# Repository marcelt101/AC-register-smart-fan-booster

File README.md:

# AC register smart fan booster

Three quiet 80 mm 5 V fans (four 60 mm fans also fit) in each 4" × 10"
supply register. The original grille is replaced by a 3D-printed frame with a
coarse wire-mesh cover, for maximum airflow. The fans run only while the furnace/AC blower runs. Home Assistant
watches your HomeKit thermostat and switches them through a Pico W on a small
carrier PCB, one board per vent. A wall toggle switch gives manual ON / OFF /
AUTO. One USB-C phone charger powers each board.

```
vent-fans/
├── README.md                  ← you are here: design, BOM, install, tuning
├── wiring.md                  ← schematic in ASCII, connector pinouts, field wiring
├── esphome/vent-fans.yaml     ← smart firmware: Pico W + Home Assistant (validated, ESPHome 2026.11)
├── micropython/main.py        ← set-and-forget firmware: MicroPython, no Wi-Fi/HA, nothing to compile (same PCB)
├── homeassistant/automation.yaml
├── frame/                     ← 3D-printable fan frame: frame.scad, make_stl.sh, stl/, README
├── sim/                       ← ngspice models, ./run_all.sh, plot.py, results.txt, plots
└── kicad/                     ← KiCad 7 project: schematic, placed board, custom Pico W part
    └── tools/                 ← generators (gen_schematic.py, gen_pcb.py, check_netlist.py)
```

## What changed from the original spec, and why

| # | Original spec | v1 | Why (evidence in `sim/`) |
|---|---|---|---|
| 1 | 100 µF across the fans, no inductor | Add **one 100 µH inductor** between the fans and the MOSFET. That makes a proper low-side buck converter. | A capacitor across a low-side-switched load gets recharged to 5 V on every PWM pulse, so the fans saw nearly full voltage at any setting: **30 % duty still gave 89 % fan current**. With the inductor the fans get smooth DC ≈ duty × 5 V (30 % → 28 %, 60 % → 56 %, ripple ≈ 80 mV). See `plot_speed_vs_duty.png`. |
| 2 | Cap only across the fans | 100 µF + 10 µF **on the 5 V rail** (input) as well | Moving caps alone (no inductor) made it worse: every pulse recharged the fans' internal capacitors through the FET with **13–19 A spikes**. The buck version peaks at **0.4 A**. See `plot_waveforms_60pct.png`. |
| 3 | 25 kHz PWM | 40 kHz | Still inaudible. A 100 µH inductor is enough at this frequency (ripple ≈ 0.15 A). |
| 4 | Speed jumps instantly | **Soft-start in firmware**: 2 % every 20 ms | Going straight from 0 to 60 % rings the LC filter: **2.1 A** inductor peak. With the slew limiter it's **0.44 A**, so a small 1 A inductor never saturates. See `plot_powerup.png`. |
| 5 | IRLZ44N / AO3400 | **SI2302CDS** (Vishay, SOT-23; AO3400A also fits) | Fully on from the Pico's 3.3 V gate drive (75 mΩ max at 2.5 V). The simulations used an AO3400A model (~32 mΩ); the SI2302CDS's higher resistance still means under 50 mW even with 4 fans at full speed, so no heatsink. Chosen because Mouser stocks it. The IRLZ44N is only specified from 4 V gate drive and is huge. |
| 6 | Breadboard wiring | **Carrier PCB, 80 × 65 mm**, through-hole resistors and capacitors, **USB-C power socket**: Pico W socketed, 4 keyed fan headers, override-switch header, DS18B20 duct-probe header | Fewer loose joints in a dusty, warm, vibrating spot. Fans unplug for cleaning. |
| 7 | Automation used `delay` + `trigger.to_state` | `for:` on the triggers, re-sync on HA restart and when the board reconnects | The old version could leave fans running after an HA restart. `for:` doesn't drop a pending off when the thermostat chatters. |
| 8 | ESPHome reboots when HA is down | `reboot_timeout: 0s`, plus an on-board fallback from the duct probe | The fans keep working (or stay safely off) with HA down. |
| 9 | 3 fans | **Header for a 4th fan**; inductor spec raised to Isat ≥ 1.5 A, diode to SS24 | Four worst-case 0.25 A fans at full speed draw 0.84 A in simulation; the 5 V rail stays ≥ 4.87 V and the FET dissipates 23 mW. |
| 10 | No manual control | **ON-OFF-ON toggle** on J6, plus a **Mode** select (Auto / Force on / Force off) and **Manual speed** in HA | The switch wins over everything. Centre position = AUTO. Works with HA down, since it is read by the Pico. |

What stayed the same: Pico W, 5 V fans, one USB charger, HA in charge, 20 s
start delay, 30 s run-on, fans **off** if anything is unplugged or the Pico is
booting (10 k gate pull-down).

### Simulation summary (`sim/results.txt`, 3 × fans, 5.1 V charger + 1 m cable + the board's fuse)

| Circuit | duty → fan current (% of full) | FET peak (60 %) | 5 V rail min (30 %) |
|---|---|---|---|
| Original spec | 30→89, 60→97, 80→99 | 0.76 A | 4.30 V |
| Caps on rail, no L | 30→76, 60→90, 80→97 | **13.3 A** | 4.49 V |
| **v1 buck** | **30→28, 60→56, 80→78** | **0.39 A** | 5.04 V |
| v1 buck, **4 × 0.25 A fans** | 60 % → 2.74 V, 100 % → 4.63 V on the fans | 0.84 A (at 100 %) | 4.87 V (at 100 %); Pico VSYS 4.59 V |

The models are approximations: the AO3400A is a VDMOS fit to its datasheet, and
each fan is modelled as a reverse diode + 1 µF + 33 Ω + 1 mH. The comparison
between circuits is what matters, not the third digit. To re-run:
`cd sim && ./run_all.sh && python3 plot.py` (needs ngspice, numpy and matplotlib).

## Bill of materials

Shopping list with what to buy marked: [`BOM.md`](BOM.md) (and [`bom.csv`](bom.csv) for a spreadsheet).

| Ref | Qty | Part | Footprint | Notes |
|---|---|---|---|---|
| U1 | 1 | Raspberry Pi Pico W, plus 2× 20-pin female headers | 2×20 THT | Socketed, so it can be swapped or reflashed |
| J7 | 1 | USB-C receptacle, 16-pin (GCT USB4105-GF-A, Mouser 640-USB4105-GF-A) | `USB_C_Receptacle_GCT_USB4105` | Phone-charger input on the left edge. Shell lugs are through-hole; only VBUS, GND, CC1, CC2 are soldered to anything (data pins unconnected). Fine tip + flux. |
| R6, R7 | 2 | 5.1 kΩ ¼ W | THT axial, 7.62 mm | CC1/CC2 pull-downs. **Must be 5.1k**: without them a USB-C charger supplies no power. |
| F1 | 1 | Resettable fuse (PTC), 1.5–2 A hold, radial | 5.1 mm leads (Bourns MF-RHT200 footprint) | Protects the wiring in the wall if something shorts |
| D2 | 1 | 1N5819 Schottky | THT DO-41 | Feeds the Pico's VSYS from the 5 V rail; stops back-feed into your PC when you flash over the Pico's micro-USB |
| Q1 | 1 | SI2302CDS-T1-GE3 N-MOSFET (Vishay; AO3400A also fits) | SOT-23 | Logic-level, 20 V 2.9 A, 75 mΩ at 2.5 V gate. Stocked at Mouser |
| L1 | 1 | 100 µH shielded power inductor, **Isat ≥ 1.5 A, DCR ≤ 0.3 Ω** | Bourns SRR1260 (12.5 mm) | Sized for 4 fans. Check Isat on the datasheet of whatever you buy. |
| D1 | 1 | SS24 Schottky, 2 A 40 V (SS14 is fine for 3 fans) | SMA | Stripe (cathode) to +5 V |
| C1, C3 | 2 | 100 µF 10 V+ low-ESR electrolytic | radial 6.3 mm, 2.5 mm pitch | C1 = input, C3 = across the fans |
| C2 | 1 | 10 µF 16 V X7R ceramic, radial leads | THT, 5 mm lead spacing | Close to Q1/D1 |
| R1 | 1 | 100 Ω ¼ W | THT axial, 7.62 mm (0.3") | gate series resistor |
| R2 | 1 | 10 kΩ ¼ W | THT axial, 7.62 mm | gate pull-down |
| J1–J4 | 3–4 | 3-pin 2.54 mm fan header (KF2510 / Molex KK style) | `FanPinHeader_1x03` | J4 only for a 4th fan. 2-pin fan plugs fit pins 1–2. |
| J5, R3 | 1 + 1 | 3-pin header + 4.7 kΩ ¼ W | THT axial, 7.62 mm | For the DS18B20 probe (R3 is its pull-up) |
| J6, R4, R5 | 1 + 2 | 3-pin header + 1 kΩ ¼ W ×2 | THT axial, 7.62 mm | Override switch. R4/R5 protect the Pico from the off-board wire. |
| SW1 | 1 | ON-OFF-ON (centre-off) SPDT toggle, e.g. MTS-103, + 3-core cable + 3-pin 2.54 mm housing | off-board | Drawn on the schematic in the dashed off-board box. Mount on the wall plate, grille or a small box. Any low-voltage switch works (3.3 V, < 1 mA). |
| — | 4 | 80 mm **5 V** fans, 25 mm thick, sleeve/hydraulic bearing, ≤ 0.25 A | | 4 fit in this vent. Pick the lowest-RPM/dBA listing. |
| RV1, C4 | 1 + 1 | 20 kΩ trimpot (10k–50k all work; Bourns 3296W footprint) + 100 nF | THT | Standalone firmware: fan speed |
| SW2 | 1 | 6 mm tactile button | THT | Standalone firmware: LEARN |
| D3, R8 | 1 + 1 | 3 mm LED + 330 Ω | THT | Standalone firmware: status |
| — | 1 | USB-C phone charger (5 V, **≥ 2 A**) + USB-C cable | | Plugs into J7 on the board. Any USB-C charger works; the board asks for plain 5 V. |
| — | 1 | Waterproof DS18B20 probe (stainless tube, 1–3 m cable) + 3-pin 2.54 mm housing | | Duct temperature: shown in HA, runs the fans when HA is down |
| — | 1 | Wire mesh, **¼" (6 mm) openings or smaller**: hardware cloth, or expanded metal for a floor vent | | Replaces the grille; cut to the size `frame/make_stl.sh` prints. See [`frame/README.md`](frame/README.md). |
| — | 8–10 | M3 × 8 countersunk screws (+ 4 × M3 × 10 and nuts for the split frame) | | Hold the printed bezel and mesh down |

Total draw per board: ≈ 0.5 A at full speed with 3 typical fans, up to ~1 A with
4 worst-case fans.

**Fans per vent:** 3 × 80 mm uses 240 mm of the 254 mm (10") opening.
**4 × 80 mm (320 mm) cannot fit**; four fans means 60 mm fans (4 × 60 = 240 mm).
Three 80 mm fans move noticeably more air than four 60 mm ones, so 3 × 80 is the
default. The board takes either.

## Build

1. **PCB**: open `kicad/vent_fans.kicad_pro` in KiCad 7 or later. The
   schematic is complete and the board is placed with nets assigned. You do the
   routing; see [Routing the board](#routing-the-board).
2. **Solder** the three surface-mount parts first: Q1 (SOT-23), D1 (SMA) and
   L1. They are all large enough for a normal iron. Then fit the through-hole
   resistors, capacitors, headers and Pico sockets. Bend the resistor leads to
   7.62 mm (0.3").
   Check the polarity of C1/C3 (+) and D1 (stripe toward the +5V side).
3. **Firmware**: in the ESPHome add-on on your Proxmox HA, create a new device
   per vent, paste `esphome/vent-fans.yaml`, change `name` / `friendly_name` at
   the top (e.g. `vent-fans-living`), add the secrets (`esphome/secrets.example.yaml`
   shows the names), plug the Pico W's own micro-USB into your PC and install.
   This is safe with the charger also plugged into J7, thanks to D2. After that,
   updates go over Wi-Fi.
4. **Bench test** before it goes in the wall. Plug the charger into the
   board's USB-C socket (J7) with the fans attached. In HA, turn on `fan.vent_fans`: the fans should ramp up over about
   a second. Measure across a fan connector (pin 2 to pin 1): ≈ 2.7 V at 1 %,
   ≈ 4 V at 60 %, ≈ 4.9 V at 100 %.
5. **Automation**: in HA, go to Developer Tools → States, filter `climate.`, and
   find your thermostat. Check that it has an `hvac_action` attribute that
   changes between `idle` and `heating`/`cooling`. HomeKit Controller thermostats
   normally do. Paste `homeassistant/automation.yaml` into a new automation and
   replace `climate.thermostat` (3 places). List each vent's fan entity in both
   fan lists.
6. **Override switch**: wire the toggle to J6 with 3 conductors: centre lug →
   pin 2 (GND), one outer lug → pin 1 (ON), the other → pin 3 (OFF). Flip it and
   watch the board's **Control source** sensor in HA change. You can also
   override from your phone with the **Mode** select, and set the override speed
   with **Manual speed** (default 100 %).
7. **Frame and mesh cover** (replaces the grille): see
   [`frame/README.md`](frame/README.md). Measure the opening, then
   `frame/make_stl.sh <width> <height> <fan> <count> <floor|wall>` writes
   print-ready STLs (base + bezel, one-piece and split), the mesh cut size and
   the screw count. PETG or ASA, no supports.

## Routing the board

The board in `kicad/vent_fans.kicad_pcb` is 80 × 65 mm and two-layer. It already
has a GND pour on both layers and a copper keep-out under the Pico W antenna.
The `Power` net class (0.8 mm tracks) covers VBUS_IN, +5V, GND, FAN- and SW. Signals
default to 0.3 mm.

1. Open the PCB and press **B** to refill zones. The ratsnest shows the 39
   connections still to route.
2. Route the **switching loop** first and keep it tiny: C2 → D1 cathode, D1
   anode → Q1 drain, Q1 source → GND via next to C2's GND pad. This is the only
   fast-edge loop on the board.
3. SW (Q1 drain / D1 anode / L1 pin 2) is the noisy node. Keep it short and
   on the top layer, with no long runs.
4. Power in: J7's four VBUS pads (A4, A9, B4, B9) → F1 → +5V. Tie the four
   GND pads (A1, A12, B1, B12) and the four shell lugs to the GND pour. Leave
   D+, D− and SBU unconnected. R6 from CC1 (A5) to GND and R7
   from CC2 (B5) to GND, kept close to the socket.
5. +5V: from F1 to C1 and C2, then on to the fan headers' pin 2 and C3+. Use
   0.8 mm or wider. Also +5V → D2 anode, and D2 cathode → Pico pin 39 (VSYS,
   top-left, second pad from the USB end). Leave Pico pin 40 (VBUS) unconnected.
6. FAN-: from L1 pin 1 to C3−, then to pin 1 of J1–J4.
7. GP15 (bottom-right Pico pad) → R1 → gate. R2 goes from gate to GND.
8. Duct probe: GP16 → J5 pin 2 → R3 → 3V3 (Pico pin 36).
9. Override: GP18 (Pico pin 24) → R4 → J6 pin 1 and GP17 (pin 22) → R5 → J6
   pin 3. Both pads are on the top row next to the antenna end. Route them on
   the bottom layer under the Pico, staying outside the keep-out, or along the
   top edge.
10. Stitch the two GND pours with a few vias, keeping them away from the
   antenna keep-out. Run **Inspect → Design Rules Checker** until it's clean.
11. **File → Fabrication Outputs → Gerbers + Drill**, zip them and order (any
   2-layer, 1.6 mm, HASL service).

`kicad/tools/` regenerates everything from one parts table, if you want to change
a part:
`python3 tools/gen_schematic.py && python3 tools/check_netlist.py && /usr/bin/python3 tools/gen_pcb.py`.
Note that this overwrites any routing you've done, so only use it before you route.

## Tuning

- **Speed**: `speed: 60` in the automation. With smooth DC the fans are much
  quieter at a given speed than with chopped PWM. Try 30–60 %.
- **Fans won't start at low speed**: raise `min_power` (0.55 ≈ 2.7 V) in
  `vent-fans.yaml`.
- **Delays**: the `for:` values in the automation (20 s on, 30 s run-on).
- **Your thermostat only shows `idle`/`heating`** (no `cooling`, or the
  attribute is missing): make the HA automation trigger on the board's
  **Duct temperature** sensor instead (same thresholds as the fallback).
- **Duct-probe fallback thresholds**: `duct_hot`, `duct_cold`, `duct_idle_low`
  and `duct_idle_high` at the top of `vent-fans.yaml`. Watch **Duct
  temperature** in HA for a day of heating or cooling, then set them between
  what you see with the blower running and with it off.

## Standalone (set-and-forget) version

The same PCB runs without Wi-Fi or Home Assistant on
[MicroPython](micropython/README.md): put MicroPython on the Pico, then copy
[`micropython/main.py`](micropython/main.py) onto it with Thonny. Nothing to
compile. A plain Pico (no W) is enough; Pico, Pico W, Pico 2 and Pico 2 W all
fit the same socket and use the same pins (only internal pins GP23/24/25/29
differ, and the firmware leaves them alone). Install steps, LED codes and how
to edit the settings are in [`micropython/README.md`](micropython/README.md).

**How it decides:** the duct probe watches the supply air. Fans start when the
air is hotter than the **heating threshold** or colder than the **cooling
threshold** for 20 s, and stop once it has been back between them (minus a
2 °C margin) for 60 s. The fans can't fool it: they move air, but they can't
make it hot or cold. It needs a duct that rests near room temperature (a
basement, crawlspace or slab, not an attic). It doesn't react to fan-only mode
(blower with no heating or cooling).

**Set-up, once:**
1. **Speed:** flip the override switch to ON. Turn the SPEED trimpot (RV1)
   until the fans are as quiet as you like while still pushing air. Flip back
   to the centre (AUTO).
2. **Heating threshold:** in winter, while the furnace is heating, press
   **LEARN** once. The LED blinks 3×.
3. **Cooling threshold:** in summer, while the AC is cooling, press **LEARN**
   once. The LED blinks 2×.

Each press sets that threshold halfway between the duct's resting temperature
(tracked while nothing is running) and the current temperature, and saves it.
Until you calibrate, the defaults are 32 °C (90 °F) and 16 °C (61 °F).
- **10 blinks:** the air isn't hot or cold enough yet to learn from, or the
  board only just started; try again in a few minutes.
- **Hold LEARN 5 s:** back to the defaults (5 blinks).
- **Status LED:** on = fans running, off = idle, slow blink = no probe (fans
  stay off in AUTO).
- **USB log:** connect Thonny to see the duct, resting and threshold
  temperatures every 30 s (see `micropython/README.md`).

## Safety and install notes

- **FAN- is not ground.** The fans' black wires sit at about 5 V minus the fan
  voltage. Never tie a fan's black wire to GND, the metal duct or the Pico.
- Keep the PCB and charger outside the duct, in the wall cavity or a small box
  next to the boot. Only the fan leads (and the probe) go into the airstream. Use
  plenum-rated cable if your local code requires it for runs inside the duct.
- Keep fans away from electric heat strips. With a heat pump or electric
  furnace, mount the fans at the register end only.
- Mount fans on foam or rubber grommets, seal the frame with foam
  weatherstrip, and have the fans blow into the room.
- **The mesh is the finger guard.** Keep its openings at ¼" (6 mm) or smaller,
  and always screw the bezel down before running the fans.
- If HA is down, the board runs the fans from the duct probe. If the probe is
  unplugged as well, the fans stay off. A Pico crash or unplugged charger also
  means fans off.
- **Duct probe**: drill a 6–7 mm hole in the side of the boot or duct, a few
  inches upstream of the fans. Push the probe tip into the airstream and seal
  the hole with foil HVAC tape. Keep it out of direct contact with the metal.

## Why Wi-Fi and not Zigbee

Your Zigbee network through HA would work, but it doesn't make this simpler.
There is no Pico + Zigbee option, and an ESP32-C6/H2 running Zigbee firmware is
harder to set up than ESPHome over Wi-Fi. It would also give up the
Mode / Manual speed / Control source entities and the on-board fallback.

The one real Zigbee simplification is a different product altogether: a Zigbee
smart plug feeding a USB charger, with the fans wired straight to USB. That
means no PCB, but also no speed control, no soft start and no override switch,
and the fans always run at full 5 V. The PCB design is better for quiet fans.

## Still open

- **Boot depth**: the frame needs about 30 mm below the floor for 25 mm fans.
- **Thermostat model**: to confirm it exposes `hvac_action` through HomeKit.

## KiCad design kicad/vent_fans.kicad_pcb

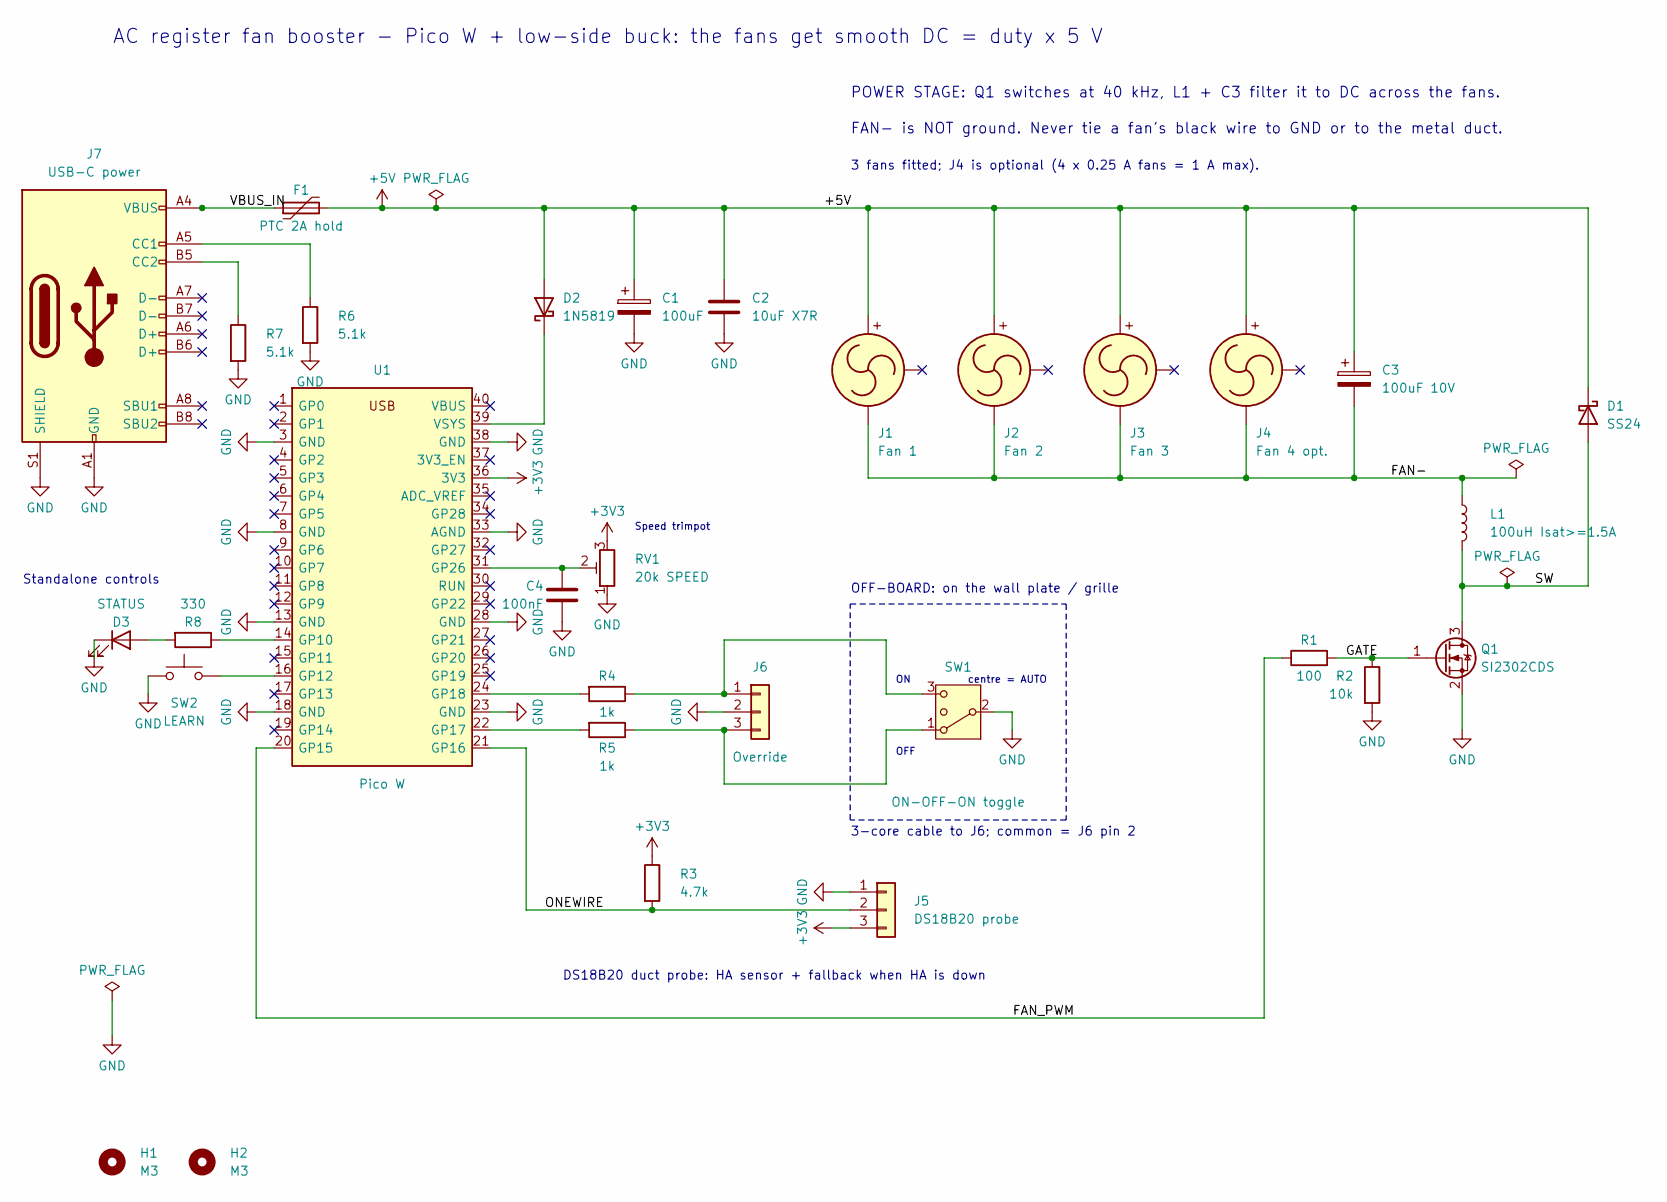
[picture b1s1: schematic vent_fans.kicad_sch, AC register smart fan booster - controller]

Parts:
C1: 100uF; CP_Radial_D6.3mm_P2.50mm
C2: 10uF X7R; C_Disc_D5.0mm_W2.5mm_P5.00mm
C3: 100uF 10V; CP_Radial_D6.3mm_P2.50mm
C4: 100nF; C_Disc_D3.0mm_W1.6mm_P2.50mm
D1: SS24; D_SMA
D2: 1N5819; D_DO-41_SOD81_P10.16mm_Horizontal
D3: STATUS; LED_D3.0mm
F1: PTC 2A hold; Fuse_Bourns_MF-RHT200
H1, H2: M3; MountingHole_3.2mm_M3
J1: Fan 1; FanPinHeader_1x03_P2.54mm_Vertical
J2: Fan 2; FanPinHeader_1x03_P2.54mm_Vertical
J3: Fan 3; FanPinHeader_1x03_P2.54mm_Vertical
J4: Fan 4 opt.; FanPinHeader_1x03_P2.54mm_Vertical
J5: DS18B20 probe; PinHeader_1x03_P2.54mm_Vertical
J6: Override; PinHeader_1x03_P2.54mm_Vertical
J7: USB-C power; USB_C_Receptacle_GCT_USB4105-xx-A_16P_TopMnt_Horizontal
L1: 100uH Isat>=1.5A; L_Bourns_SRR1260
Q1: SI2302CDS; SOT-23
R1: 100; R_Axial_DIN0207_L6.3mm_D2.5mm_P7.62mm_Horizontal
R2: 10k; R_Axial_DIN0207_L6.3mm_D2.5mm_P7.62mm_Horizontal
R3: 4.7k; R_Axial_DIN0207_L6.3mm_D2.5mm_P7.62mm_Horizontal
R4, R5: 1k; R_Axial_DIN0207_L6.3mm_D2.5mm_P7.62mm_Horizontal
R6, R7: 5.1k; R_Axial_DIN0207_L6.3mm_D2.5mm_P7.62mm_Horizontal
R8: 330; R_Axial_DIN0207_L6.3mm_D2.5mm_P7.62mm_Horizontal
RV1: 20k SPEED; Potentiometer_Bourns_3296W_Vertical
SW1: ON-OFF-ON toggle
SW2: LEARN; SW_PUSH_6mm
U1: Pico W; RaspberryPi_PicoW_THT

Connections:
+3V3: J5.3, R3.1, RV1.3, U1.36 (3V3)
+5V: C1.1, C2.1, C3.1, D1.1 (K), D2.2 (A), F1.2, J1.2 (+), J2.2 (+), J3.2 (+), J4.2 (+)
CC1: J7.A5 (CC1), R6.1
CC2: J7.B5 (CC2), R7.1
FAN-: C3.2, J1.1 (-), J2.1 (-), J3.1 (-), J4.1 (-), L1.1
FAN_PWM: R1.1, U1.20 (GP15)
GATE: Q1.1 (G), R1.2, R2.1
GND: C1.2, C2.2, C4.2, D3.1 (K), J5.1, J6.2, J7.A1 (GND), J7.A12 (GND), J7.B1 (GND), J7.B12 (GND), J7.S1 (SHIELD), Q1.2 (S), R2.2, R6.2, R7.2, RV1.1, SW1.2 (3), SW2.1, U1.3 (GND), U1.8 (GND), U1.13 (GND), U1.18 (GND), U1.23 (GND), U1.28 (GND), U1.33 (AGND), U1.38 (GND)
LEARN: SW2.2, U1.16 (GP12)
LED: R8.1, U1.14 (GP10)
LED_A: D3.2 (A), R8.2
ONEWIRE: J5.2, R3.2, U1.21 (GP16)
OVR_OFF: R5.2, U1.22 (GP17)
OVR_OFF_J: J6.3, R5.1, SW1.1
OVR_ON: R4.2, U1.24 (GP18)
OVR_ON_J: J6.1, R4.1, SW1.3 (4)
SPEED_POT: C4.1, RV1.2, U1.31 (GP26)
SW: D1.2 (A), L1.2, Q1.3 (D)
VBUS_IN: F1.1, J7.A4 (VBUS), J7.A9 (VBUS), J7.B4 (VBUS), J7.B9 (VBUS)
VSYS: D2.1 (K), U1.39 (VSYS)

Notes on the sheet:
OFF-BOARD: on the wall plate / grille
3-core cable to J6; common = J6 pin 2
OFF
centre = AUTO
Standalone controls
Speed trimpot
AC register fan booster - Pico W + low-side buck: the fans get smooth DC = duty x 5 V
POWER STAGE: Q1 switches at 40 kHz, L1 + C3 filter it to DC across the fans.
FAN- is NOT ground. Never tie a fan's black wire to GND or to the metal duct.
3 fans fitted; J4 is optional (4 x 0.25 A fans = 1 A max).
DS18B20 duct probe: HA sensor + fallback when HA is down

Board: 2 copper layers, 30 parts (0 on the bottom side), 20 nets, no tracks yet.

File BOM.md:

# Bill of materials (per vent)

Quantities are for **one vent** (one controller board + one frame). Multiply
for more vents. The same list is in [`bom.csv`](bom.csv) for a spreadsheet.

**🛒 = buy.** Resistors and capacitors are at the bottom; you already have
those.

## To buy

| 🛒 | Ref | Qty | Part | Spec / example | Notes |
|---|---|---|---|---|---|
| **Controller** ||||||
| 🛒 | U1 | 1 | Raspberry Pi Pico W | Pico **WH** (headers pre-soldered) is easiest | W (Wi-Fi) for the smart firmware. A plain Pico / Pico H is enough for the standalone firmware |
| 🛒 | — | 2 | Female header 1×20, 2.54 mm | straight | Socket for the Pico |
| **Power stage** ||||||
| 🛒 | Q1 | 1 | **SI2302CDS-T1-GE3** N-MOSFET (Vishay), 20 V 2.9 A, 75 mΩ at 2.5 V gate | SOT-23 (SMD) | Stocked at Mouser. Same pinout as the AO3400A it replaces. Buy a few spares |
| 🛒 | D1 | 1 | SS24 Schottky, 2 A 40 V | SMA (SMD) | SS14 OK for 3 fans. Not a 1N4148 |
| 🛒 | L1 | 1 | 100 µH shielded inductor, Isat ≥ 1.5 A, DCR ≤ 0.3 Ω | 12 × 12 mm SMD, e.g. Bourns SRR1260-101M | Check Isat on the datasheet |
| **Power input** ||||||
| 🛒 | J7 | 1 | USB-C receptacle, 16-pin | **GCT USB4105-GF-A** (Mouser 640-USB4105-GF-A) | Only VBUS, GND, CC1, CC2 are used. Fine tip + flux; see note below |
| 🛒 | F1 | 1 | Resettable fuse (PTC), 1.5–2 A hold | radial, 5.1 mm leads (MF-R160 / MF-RHT200) | |
| 🛒 | D2 | 1 | 1N5819 Schottky | DO-41 through-hole | |
| 🛒 | — | 1 | USB-C phone charger | 5 V, **≥ 2 A** | |
| 🛒 | — | 1 | USB-C cable | length to suit | |
| **Connectors** ||||||
| 🛒 | J1–J4 | 4 | Fan header, 3-pin 2.54 mm | KF2510 / Molex KK style, vertical | J4 only for a 4th fan |
| 🛒 | J5, J6 | 2 | Pin header 1×3, 2.54 mm | break from a 40-pin strip | Probe and switch |
| 🛒 | — | 1 kit | KF2510 / Dupont 3-pin housings + crimp pins | | For fans, probe and switch cable |
| **Fans, sensor, switch** ||||||
| 🛒 | — | 4 (+1) | 80 mm fan, **5 V DC** | 80×80×25 mm, ~1700 rpm, ~25 dB, ≤ 0.25 A | 4 fit in your vent; +1 spare |
| 🛒 | — | 1 | DS18B20 **waterproof probe** (chip sealed in a steel tube on a cable) | **DFRobot DFR0198** at Mouser (Adafruit 381 also fits) | Not the bare TO-92 chip. Wires: red 3V3, black GND, yellow/white/green data (check the listing) |
| 🛒 | SW1 | 1 | Toggle switch ON-OFF-ON (SPDT centre-off) | e.g. MTS-103 | Off-board |
| 🛒 | — | as needed | 3-core cable, 22–26 AWG | alarm / thermostat wire | Switch to J6 |
| **Standalone controls** (speed, LEARN, status; the smart firmware ignores them) ||||||
| have | RV1 | 1 | 20 kΩ trimpot (10k–50k all work) | Bourns 3296W footprint (e.g. 3296W-1-203LF) | Sets fan speed in standalone mode. You have 20k ones; match the footprint to their shape in KiCad |
| 🛒 | SW2 | 1 | 6 × 6 mm through-hole tactile button (4-pin) | any standard 6 mm tact switch | LEARN button |
| 🛒 | D3 | 1 | 3 mm LED, any colour | through-hole | Status. Long leg (anode) to R8 |
| **Frame** ||||||
| 🛒 | — | 1 | Wire mesh, **¼" (6 mm) openings or smaller** | hardware cloth (wall) or expanded metal 1–1.5 mm (floor) | Cut to size: 264 × 98 mm nominal |
| 🛒 | — | 10 | M3 × 8 countersunk screws | stainless | 8 for 3 fans, 10 for 4 |
| 🛒 | — | 4 | M3 × 10 screws + nuts | | Split frame only |
| 🛒 | — | 1 | 3D print, PETG or ASA | base + bezel (+ tabs) | Not PLA |
| optional | — | 12 | Rubber fan grommets / foam washers | | Quieter |
| optional | — | 1 | Thin foam weatherstrip | 3–6 mm, adhesive | Seals the flange |
| **PCB** ||||||
| 🛒 | — | 1 | PCB fab, 80 × 65 mm, 2-layer, 1.6 mm | JLCPCB / PCBWay etc. | Minimum order is usually 5 |
| optional | — | 1 | Crimp tool (e.g. SN-28B) | | Only if you don't have one |

## Already have (resistors and capacitors)

| Ref | Qty | Part | Spec | Notes |
|---|---|---|---|---|
| R1 | 1 | 100 Ω | ¼ W axial | Gate series |
| R2 | 1 | 10 kΩ | ¼ W axial | Gate pull-down |
| R3 | 1 | 4.7 kΩ | ¼ W axial | 1-Wire pull-up |
| R4, R5 | 2 | 1 kΩ | ¼ W axial | Switch line protection |
| R6, R7 | 2 | **5.1 kΩ** | ¼ W axial | USB-C CC pull-downs. **Must be 5.1k**; check your kit has it |
| C1, C3 | 2 | 100 µF electrolytic | 10 V+, low-ESR, radial 6.3 mm / 2.5 mm | Watch polarity |
| C2 | 1 | 10 µF **ceramic** | 16 V+, X7R/X5R, radial, 5 mm leads | Check it's ceramic, not electrolytic |
| R8 | 1 | 330 Ω | ¼ W axial | Status LED resistor |
| C4 | 1 | 100 nF ceramic | radial, 2.5 mm leads | Smooths the speed trimpot reading |

**USB-C socket soldering:** the USB4105's signal pads are 0.3 mm at 0.5 mm
pitch. Only VBUS, GND, CC1 (A5) and CC2 (B5) are connected. The data pads (D+, D−,
SBU) are left unconnected, so a solder bridge from CC1/CC2 onto them is harmless.
Do make sure **CC2 (B5) isn't bridged to the VBUS pad** next to it.

Two to double-check in your stock: **5.1 kΩ** (many kits only have 4.7k and
5.6k, and USB-C chargers won't turn on without 5.1k) and a **10 µF ceramic** with
leads (many kits only have small ceramics, ≤ 1 µF). If either is missing,
add it to the order.

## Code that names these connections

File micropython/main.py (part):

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SETTINGS_FILE = "settings.json"

# ---- Pins (same on Pico, Pico W, Pico 2, Pico 2 W) --------------------------
PIN_FAN_PWM = 15         # Q1 gate (low-side buck)
PIN_ONEWIRE = 16         # J5, DS18B20 duct probe
PIN_SW_OFF = 17          # J6 pin 3, override switch "force off" (to GND)
PIN_SW_ON = 18           # J6 pin 1, override switch "force on" (to GND)
PIN_LEARN = 12           # SW2 LEARN button (to GND)
PIN_LED = 10             # D3 status LED
PIN_POT = 26             # RV1 speed trimpot wiper (ADC0)

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    import ds18x20

    led = Pin(PIN_LED, Pin.OUT, value=0)
    learn_btn = Pin(PIN_LEARN, Pin.IN, Pin.PULL_UP)

    # Safe mode: LEARN held at power-up -> don't start (so Thonny can connect).
    if learn_btn.value() == 0:
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            sleep_ms(150)
        return

    pwm = PWM(Pin(PIN_FAN_PWM))
    pwm.freq(PWM_FREQ)
    pwm.duty_u16(0)
    sw_on = Pin(PIN_SW_ON, Pin.IN, Pin.PULL_UP)
    sw_off = Pin(PIN_SW_OFF, Pin.IN, Pin.PULL_UP)
    pot_adc = ADC(PIN_POT)
    ds = ds18x20.DS18X20(onewire.OneWire(Pin(PIN_ONEWIRE)))

    settings = load_settings()
    ctl = Controller(settings["heat"], settings["cool"])
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    except Exception as e:      # never leave the fans in a random state
        try:
            from machine import Pin, reset
            Pin(PIN_FAN_PWM, Pin.OUT, value=0)
            print("Error:", e, "- restarting in 5 s")
            sleep_ms(5000)
            reset()
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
